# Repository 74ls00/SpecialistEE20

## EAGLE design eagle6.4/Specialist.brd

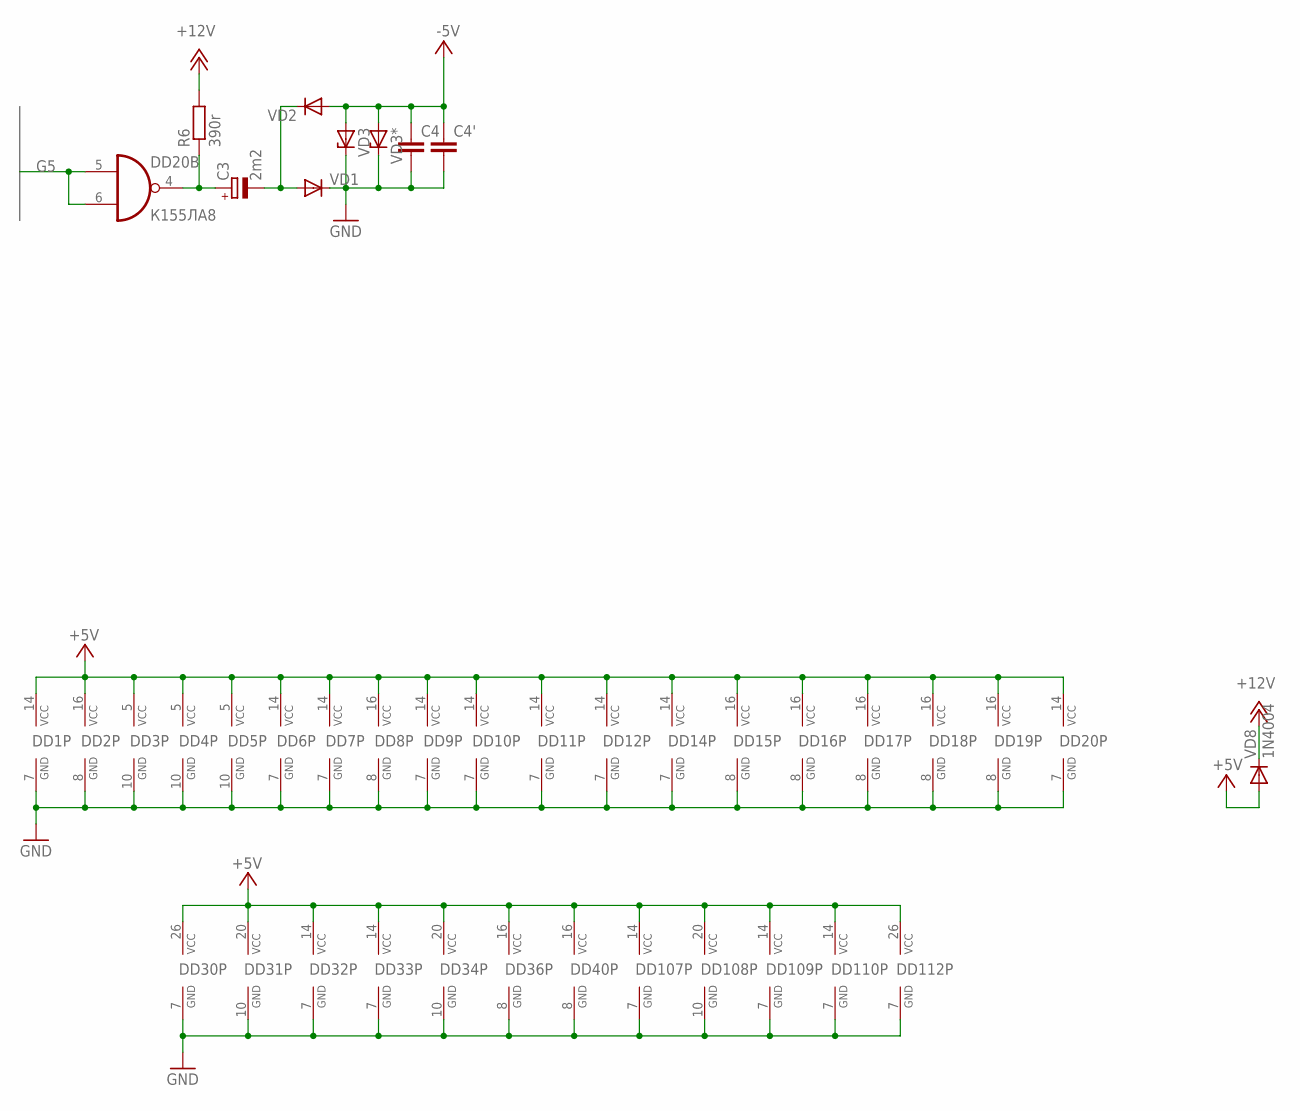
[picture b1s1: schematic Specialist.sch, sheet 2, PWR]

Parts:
C3: 2m2; E2,5-5
C4, C4': C-EUC1206; C1206
DD1, DD9: К155ЛН1; DIL14
DD2, DD8: К155ИЕ7; DIL16
DD3, DD4, DD5: К155ИЕ5; DIL14
DD6, DD107, DD110: К155ЛЕ1; DIL14
DD7: К155ЛА4; DIL14
DD10: К155ЛА2; DIL14
DD11, DD14: К155ЛА3; DIL14
DD12: К155ТМ2; DIL14
DD15, DD16, DD17, DD18: К155КП2; DIL16
DD19: К155ЛП10; DIL16
DD20: К155ЛА8; DIL14
DD30, DD112: КР580ВВ55; DIL40
DD31, DD108: К555ИР22; DIL20
DD32, DD33, DD109: К555ИР16; DIL14
DD34: К555АП6; DIL20
DD36, DD40: К155ИД4; DIL16
R6: 390r; 0411/15
VD1, VD2: DIODE-SOD80C; SOD80C
VD3, VD3*: ZENER-DIODESOD80C; SOD80C
VD8: 1N4004; DO41-10

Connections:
+5V: DD1.14 (VCC), DD2.16 (VCC), DD3.5 (VCC), DD4.5 (VCC), DD5.5 (VCC), DD6.14 (VCC), DD7.14 (VCC), DD8.16 (VCC), DD9.14 (VCC), DD10.14 (VCC), DD11.14 (VCC), DD12.14 (VCC), DD14.14 (VCC), DD15.16 (VCC), DD16.16 (VCC), DD17.16 (VCC), DD18.16 (VCC), DD19.16 (VCC), DD20.14 (VCC), DD30.26 (VCC), DD31.20 (VCC), DD32.14 (VCC), DD33.14 (VCC), DD34.20 (VCC), DD36.16 (VCC), DD40.16 (VCC), DD107.14 (VCC), DD108.20 (VCC), DD109.14 (VCC), DD110.14 (VCC), DD112.26 (VCC), VD8.A; also elsewhere on the board
+12V: R6.2, VD8.C; also elsewhere on the board
-5V: C4.1, C4'.1, VD2.A, VD3.A, VD3*.A; also elsewhere on the board
G5: DD20.5 (I0), DD20.6 (I1); also elsewhere on the board
GND: C4.2, C4'.2, DD1.7 (GND), DD2.8 (GND), DD3.10 (GND), DD4.10 (GND), DD5.10 (GND), DD6.7 (GND), DD7.7 (GND), DD8.8 (GND), DD9.7 (GND), DD10.7 (GND), DD11.7 (GND), DD12.7 (GND), DD14.7 (GND), DD15.8 (GND), DD16.8 (GND), DD17.8 (GND), DD18.8 (GND), DD19.8 (GND), DD20.7 (GND), DD30.7 (GND), DD31.10 (GND), DD32.7 (GND), DD33.7 (GND), DD34.10 (GND), DD36.8 (GND), DD40.8 (GND), DD107.7 (GND), DD108.10 (GND), DD109.7 (GND), DD110.7 (GND), DD112.7 (GND), VD1.C, VD3.C, VD3*.C; also elsewhere on the board
unnamed: C3.+, DD20.4 (O), R6.1
unnamed: C3.-, VD1.A, VD2.C

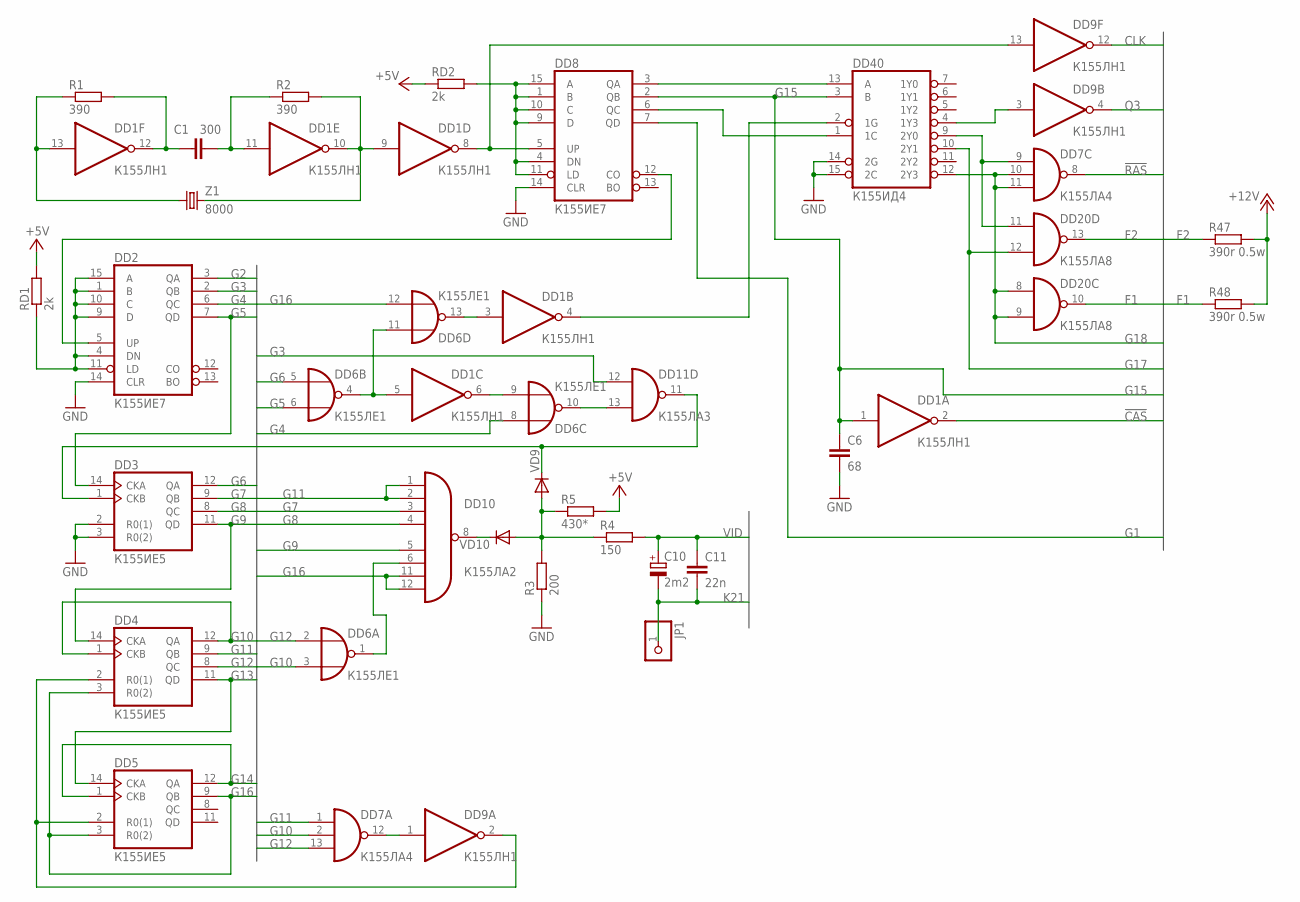
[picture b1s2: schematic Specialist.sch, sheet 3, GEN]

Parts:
C1: 300; C0805
C6: 68; C0805
C10: 2m2; E2,5-5
C11: 22n; C0805
DD1, DD9: К155ЛН1; DIL14
DD2, DD8: К155ИЕ7; DIL16
DD3, DD4, DD5: К155ИЕ5; DIL14
DD6: К155ЛЕ1; DIL14
DD7: К155ЛА4; DIL14
DD10: К155ЛА2; DIL14
DD11: К155ЛА3; DIL14
DD20: К155ЛА8; DIL14
DD40: К155ИД4; DIL16
JP1: PINHD-1X1; 1X01
R1, R2: 390; M1206
R3: 200; M1206
R4: 150; M1206
R5: 430*; M1206
R47, R48: 390r 0.5w; 0411/15
RD1, RD2: 2k; M1206
VD9, VD10: DIODE-SOD80C; SOD80C
Z1: 8000; HC49/S

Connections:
!CAS: DD1.2 (O); also elsewhere on the board
!RAS: DD7.8 (O); also elsewhere on the board
+5V: R5.2, RD1.2, RD2.1; also elsewhere on the board
+12V: R47.2, R48.2; also elsewhere on the board
CLK: DD9.12 (O); also elsewhere on the board
F1: DD20.10 (O), R48.1; also elsewhere on the board
F2: DD20.13 (O), R47.1; also elsewhere on the board
G1: DD8.7 (QD); also elsewhere on the board
G2: DD2.3 (QA); also elsewhere on the board
G3: DD2.2 (QB), DD11.12 (I0); also elsewhere on the board
G4: DD2.6 (QC), DD6.8 (I0); also elsewhere on the board
G5: DD2.7 (QD), DD3.14 (CKA), DD6.6 (I1); also elsewhere on the board
G6: DD3.12 (QA), DD6.5 (I0); also elsewhere on the board
G7: DD3.9 (QB), DD10.3 (I2); also elsewhere on the board
G8: DD3.8 (QC), DD10.4 (I3); also elsewhere on the board
G9: DD3.11 (QD), DD4.14 (CKA), DD10.5 (I4); also elsewhere on the board
G10: DD4.1 (CKB), DD4.12 (QA), DD6.3 (I1), DD7.2 (I1); also elsewhere on the board
G11: DD4.9 (QB), DD7.1 (I0), DD10.1 (I0), DD10.2 (I1); also elsewhere on the board
G12: DD4.8 (QC), DD6.2 (I0), DD7.13 (I2); also elsewhere on the board
G13: DD4.11 (QD), DD5.14 (CKA); also elsewhere on the board
G14: DD5.1 (CKB), DD5.12 (QA); also elsewhere on the board
G15: C6.1, DD1.1 (I), DD8.2 (QB), DD40.3 (B); also elsewhere on the board
G16: DD4.3 (R0(2)), DD5.3 (R0(2)), DD5.9 (QB), DD6.12 (I1), DD10.11 (I6), DD10.12 (I7); also elsewhere on the board
G17: DD20.12 (I1), DD40.10 (2Y1); also elsewhere on the board
G18: DD7.10 (I1), DD7.11 (I2), DD20.8 (I0), DD20.9 (I1), DD40.12 (2Y3); also elsewhere on the board
GND: C6.2, DD2.14 (CLR), DD3.2 (R0(1)), DD3.3 (R0(2)), DD8.14 (CLR), DD40.14 (2G), DD40.15 (2C), R3.1; also elsewhere on the board
K21: C10.-, C11.2, JP1.1
unnamed: DD6.10 (O), DD11.13 (I1)
unnamed: DD1.5 (I), DD6.4 (O), DD6.11 (I0)
unnamed: DD1.13 (I), R1.1, Z1.1
unnamed: DD9.3 (I), DD40.4 (1Y3)
unnamed: C1.1, DD1.12 (O), R1.2
unnamed: DD1.9 (I), DD1.10 (O), R2.2, Z1.2
unnamed: C1.2, DD1.11 (I), R2.1
unnamed: DD1.8 (O), DD8.5 (UP), DD9.13 (I)
unnamed: DD2.5 (UP), DD8.12 (CO)
unnamed: DD6.1 (O), DD10.6 (I5)
unnamed: DD1.6 (O), DD6.9 (I1)
unnamed: DD1.3 (I), DD6.13 (O)
unnamed: DD4.2 (R0(1)), DD5.2 (R0(1)), DD9.2 (O)
unnamed: DD7.9 (I0), DD20.11 (I0), DD40.9 (2Y0)
unnamed: DD8.3 (QA), DD40.13 (A)
unnamed: DD8.6 (QC), DD40.1 (1C)
unnamed: DD1.4 (O), DD40.2 (1G)
unnamed: DD10.8 (O), VD10.C
unnamed: DD3.1 (CKB), DD11.11 (O), VD9.C
unnamed: R3.2, R4.1, R5.1, VD9.A, VD10.A
unnamed: DD2.1 (B), DD2.4 (DN), DD2.9 (D), DD2.10 (C), DD2.11 (LD), DD2.15 (A), RD1.1
unnamed: DD7.12 (O), DD9.1 (I)
unnamed: DD8.1 (B), DD8.4 (DN), DD8.9 (D), DD8.10 (C), DD8.11 (LD), DD8.15 (A), RD2.2
Q3: DD9.4 (O); also elsewhere on the board
VID: C10.+, C11.1, R4.2; also elsewhere on the board

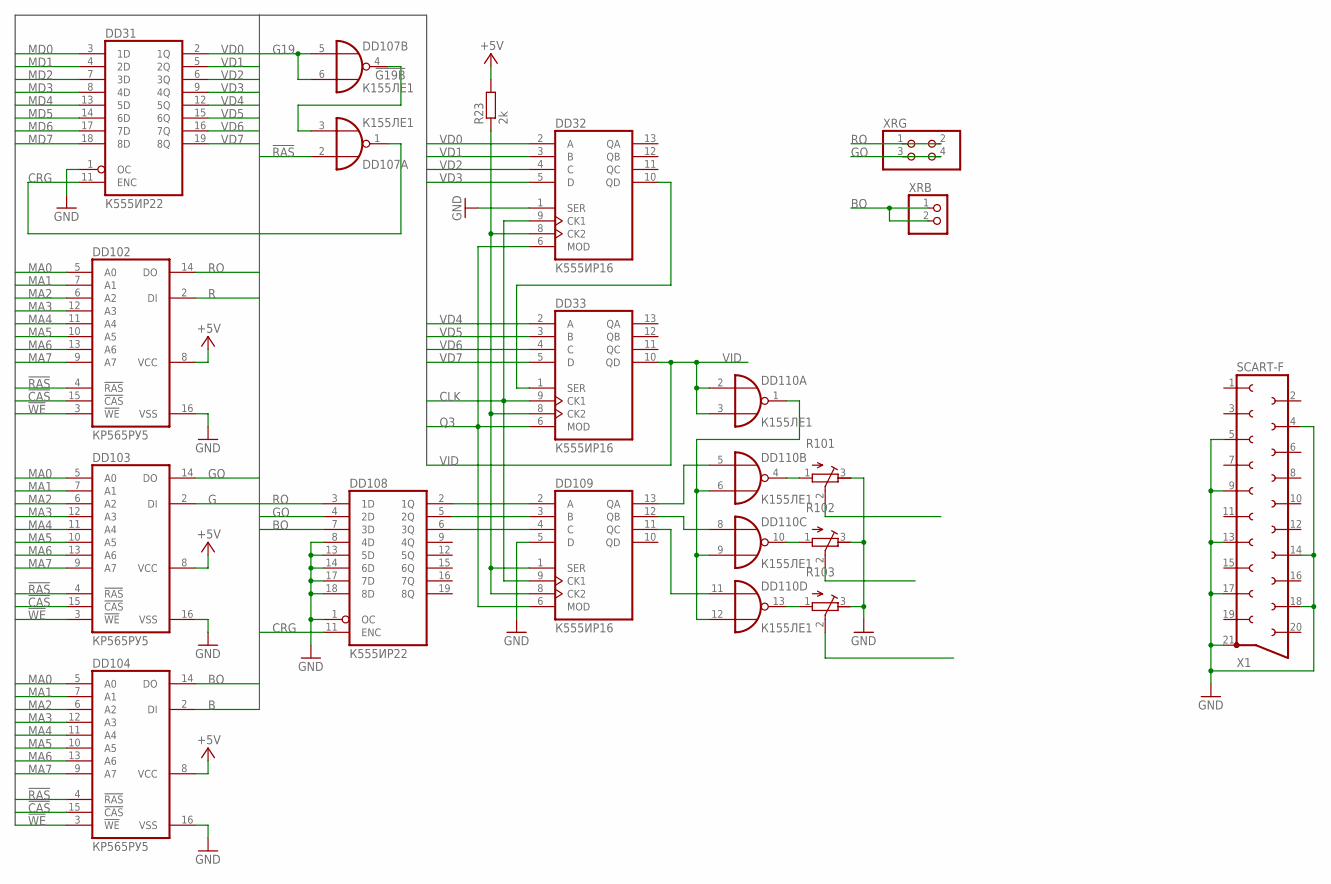
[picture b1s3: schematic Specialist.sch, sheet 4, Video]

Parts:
DD31, DD108: К555ИР22; DIL20
DD32, DD33, DD109: К555ИР16; DIL14
DD102, DD103, DD104: КР565РУ5; DIL16
DD107, DD110: К155ЛЕ1; DIL14
R23: 2k; M1206
R101, R102, R103: R-TRIMM3296W; RTRIM3296W
X1: SCART-F
XRB: PINHD-1X2; 2X01
XRG: PINHD-2X2; 2X02

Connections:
!CAS: DD102.15 (!CAS), DD103.15 (!CAS), DD104.15 (!CAS); also elsewhere on the board
!G19B: DD107.3 (I1), DD107.4 (O)
!RAS: DD102.4 (!RAS), DD103.4 (!RAS), DD104.4 (!RAS), DD107.2 (I0); also elsewhere on the board
!WE: DD102.3 (!WE), DD103.3 (!WE), DD104.3 (!WE); also elsewhere on the board
+5V: DD102.8 (VCC), DD103.8 (VCC), DD104.8 (VCC), R23.2; also elsewhere on the board
B: DD104.2 (DI); also elsewhere on the board
BO: DD104.14 (DO), DD108.7 (3D), XRB.1, XRB.2; also elsewhere on the board
CLK: DD32.9 (CK1), DD33.9 (CK1), DD109.9 (CK1); also elsewhere on the board
CRG: DD31.11 (ENC), DD107.1 (O), DD108.11 (ENC)
G: DD103.2 (DI); also elsewhere on the board
G19: DD107.5 (I0), DD107.6 (I1); also elsewhere on the board
GND: DD31.1 (OC), DD32.1 (SER), DD102.16 (VSS), DD103.16 (VSS), DD104.16 (VSS), DD108.1 (OC), DD108.8 (4D), DD108.13 (5D), DD108.14 (6D), DD108.17 (7D), DD108.18 (8D), DD109.5 (D), R101.3 (E), R102.3 (E), R103.3 (E), X1.4, X1.5, X1.9, X1.13, X1.14, X1.17, X1.18, X1.21; also elsewhere on the board
GO: DD103.14 (DO), DD108.4 (2D), XRG.3, XRG.4; also elsewhere on the board
MA0: DD102.5 (A0), DD103.5 (A0), DD104.5 (A0); also elsewhere on the board
MA1: DD102.7 (A1), DD103.7 (A1), DD104.7 (A1); also elsewhere on the board
MA2: DD102.6 (A2), DD103.6 (A2), DD104.6 (A2); also elsewhere on the board
MA3: DD102.12 (A3), DD103.12 (A3), DD104.12 (A3); also elsewhere on the board
MA4: DD102.11 (A4), DD103.11 (A4), DD104.11 (A4); also elsewhere on the board
MA5: DD102.10 (A5), DD103.10 (A5), DD104.10 (A5); also elsewhere on the board
MA6: DD102.13 (A6), DD103.13 (A6), DD104.13 (A6); also elsewhere on the board
MA7: DD102.9 (A7), DD103.9 (A7), DD104.9 (A7); also elsewhere on the board
MD0: DD31.3 (1D); also elsewhere on the board
MD1: DD31.4 (2D); also elsewhere on the board
MD2: DD31.7 (3D); also elsewhere on the board
MD3: DD31.8 (4D); also elsewhere on the board
MD4: DD31.13 (5D); also elsewhere on the board
MD5: DD31.14 (6D); also elsewhere on the board
MD6: DD31.17 (7D); also elsewhere on the board
MD7: DD31.18 (8D); also elsewhere on the board
unnamed: DD32.10 (QD), DD33.1 (SER)
unnamed: DD110.1 (O), DD110.6 (I1), DD110.9 (I1), DD110.12 (I1)
unnamed: DD108.2 (1Q), DD109.2 (A)
unnamed: DD108.5 (2Q), DD109.3 (B)
unnamed: DD108.6 (3Q), DD109.4 (C)
unnamed: DD109.13 (QA), DD110.5 (I0)
unnamed: DD109.12 (QB), DD110.8 (I0)
unnamed: DD109.11 (QC), DD110.11 (I0)
unnamed: DD110.4 (O), R101.1 (A)
unnamed: DD110.10 (O), R102.1 (A)
unnamed: DD110.13 (O), R103.1 (A)
Q3: DD32.6 (MOD), DD33.6 (MOD), DD109.6 (MOD); also elsewhere on the board
R: DD102.2 (DI); also elsewhere on the board
R2: DD32.8 (CK2), DD33.8 (CK2), DD109.1 (SER), DD109.8 (CK2), R23.1
RO: DD102.14 (DO), DD108.3 (1D), XRG.1, XRG.2; also elsewhere on the board
VD0: DD31.2 (1Q), DD32.2 (A)
VD1: DD31.5 (2Q), DD32.3 (B)
VD2: DD31.6 (3Q), DD32.4 (C)
VD3: DD31.9 (4Q), DD32.5 (D)
VD4: DD31.12 (5Q), DD33.2 (A)
VD5: DD31.15 (6Q), DD33.3 (B)
VD6: DD31.16 (7Q), DD33.4 (C)
VD7: DD31.19 (8Q), DD33.5 (D)
VID: DD33.10 (QD), DD110.2 (I0), DD110.3 (I1); also elsewhere on the board

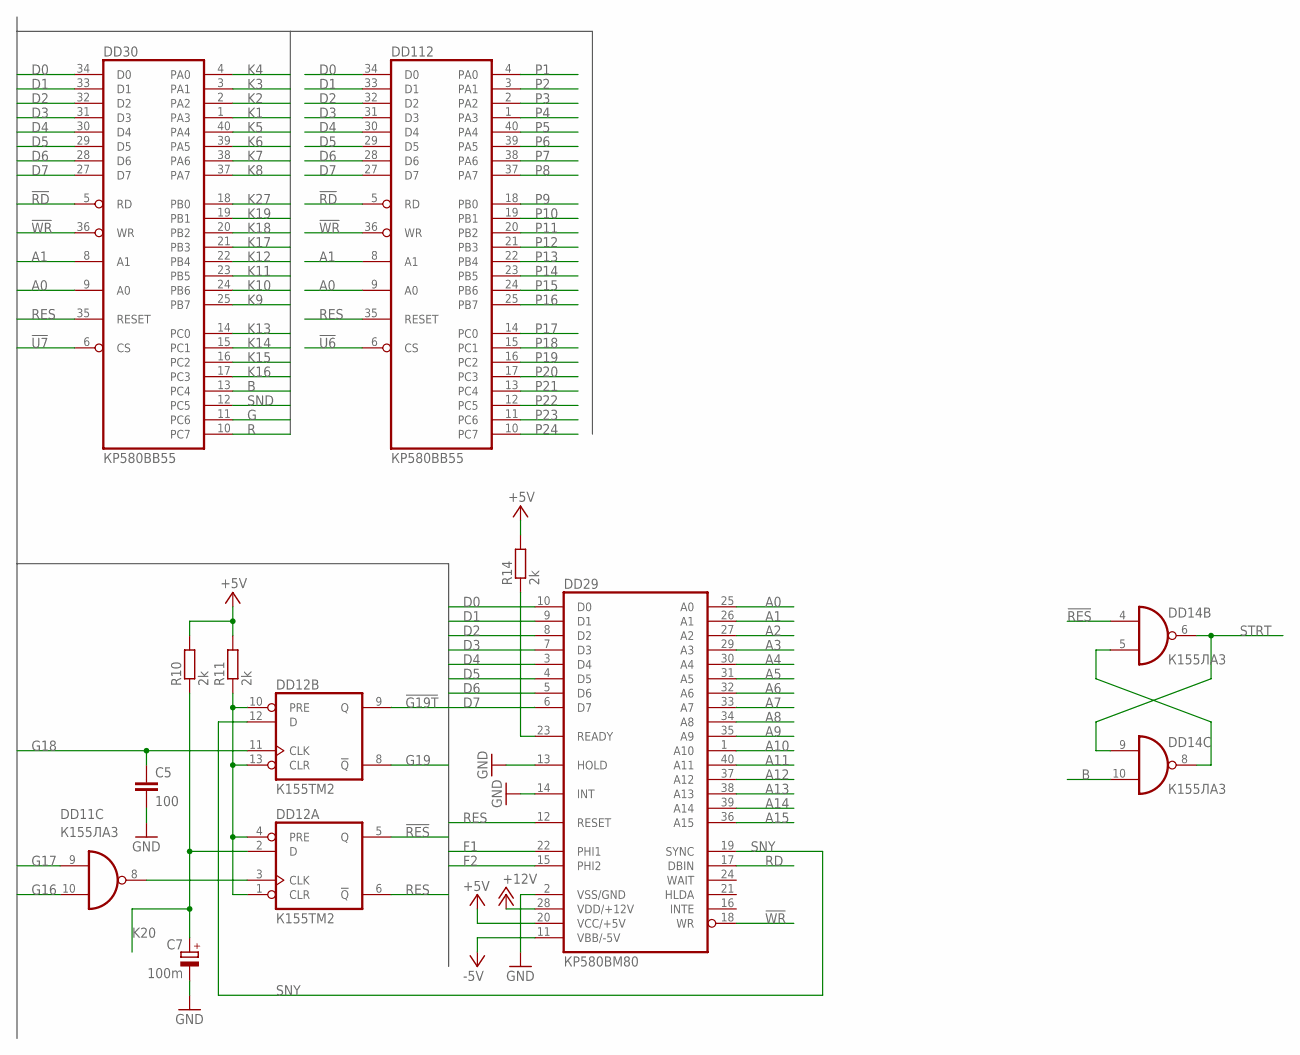
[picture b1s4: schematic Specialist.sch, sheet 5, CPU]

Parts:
C5: 100; C0805
C7: 100m; E2,5-5
DD11, DD14: К155ЛА3; DIL14
DD12: К155ТМ2; DIL14
DD29: КР580ВМ80; DIL40
DD30, DD112: КР580ВВ55; DIL40
R10, R11, R14: 2k; M1206

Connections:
!G19T: DD12.9 (Q); also elsewhere on the board
!RD: DD30.5 (RD), DD112.5 (RD); also elsewhere on the board
!RES: DD12.5 (Q), DD14.4 (I0)
!U6: DD112.6 (CS); also elsewhere on the board
!U7: DD30.6 (CS); also elsewhere on the board
!WR: DD29.18 (WR), DD30.36 (WR), DD112.36 (WR); also elsewhere on the board
+5V: DD29.20 (VCC/+5V), R10.2, R11.2, R14.2; also elsewhere on the board
+12V: DD29.28 (VDD/+12V); also elsewhere on the board
-5V: DD29.11 (VBB/-5V); also elsewhere on the board
A0: DD29.25 (A0), DD30.9 (A0), DD112.9 (A0); also elsewhere on the board
A1: DD29.26 (A1), DD30.8 (A1), DD112.8 (A1); also elsewhere on the board
A2: DD29.27 (A2); also elsewhere on the board
A3: DD29.29 (A3); also elsewhere on the board
A4: DD29.30 (A4); also elsewhere on the board
A5: DD29.31 (A5); also elsewhere on the board
A6: DD29.32 (A6); also elsewhere on the board
A7: DD29.33 (A7); also elsewhere on the board
A8: DD29.34 (A8); also elsewhere on the board
A9: DD29.35 (A9); also elsewhere on the board
A10: DD29.1 (A10); also elsewhere on the board
A11: DD29.40 (A11); also elsewhere on the board
A12: DD29.37 (A12); also elsewhere on the board
A13: DD29.38 (A13); also elsewhere on the board
A14: DD29.39 (A14); also elsewhere on the board
A15: DD29.36 (A15); also elsewhere on the board
B: DD14.10 (I1), DD30.13 (PC4); also elsewhere on the board
D0: DD29.10 (D0), DD30.34 (D0), DD112.34 (D0); also elsewhere on the board
D1: DD29.9 (D1), DD30.33 (D1), DD112.33 (D1); also elsewhere on the board
D2: DD29.8 (D2), DD30.32 (D2), DD112.32 (D2); also elsewhere on the board
D3: DD29.7 (D3), DD30.31 (D3), DD112.31 (D3); also elsewhere on the board
D4: DD29.3 (D4), DD30.30 (D4), DD112.30 (D4); also elsewhere on the board
D5: DD29.4 (D5), DD30.29 (D5), DD112.29 (D5); also elsewhere on the board
D6: DD29.5 (D6), DD30.28 (D6), DD112.28 (D6); also elsewhere on the board
D7: DD29.6 (D7), DD30.27 (D7), DD112.27 (D7); also elsewhere on the board
F1: DD29.22 (PHI1); also elsewhere on the board
F2: DD29.15 (PHI2); also elsewhere on the board
G: DD30.11 (PC6); also elsewhere on the board
G16: DD11.10 (I1); also elsewhere on the board
G17: DD11.9 (I0); also elsewhere on the board
G18: C5.1, DD12.11 (CLK); also elsewhere on the board
G19: DD12.8 (!Q); also elsewhere on the board
GND: C5.2, C7.-, DD29.2 (VSS/GND), DD29.13 (HOLD), DD29.14 (INT); also elsewhere on the board
K1: DD30.1 (PA3); also elsewhere on the board
K2: DD30.2 (PA2); also elsewhere on the board
K3: DD30.3 (PA1); also elsewhere on the board
K4: DD30.4 (PA0); also elsewhere on the board
K5: DD30.40 (PA4); also elsewhere on the board
K6: DD30.39 (PA5); also elsewhere on the board
K7: DD30.38 (PA6); also elsewhere on the board
K8: DD30.37 (PA7); also elsewhere on the board
K9: DD30.25 (PB7); also elsewhere on the board
K10: DD30.24 (PB6); also elsewhere on the board
K11: DD30.23 (PB5); also elsewhere on the board
K12: DD30.22 (PB4); also elsewhere on the board
K13: DD30.14 (PC0); also elsewhere on the board
K14: DD30.15 (PC1); also elsewhere on the board
K15: DD30.16 (PC2); also elsewhere on the board
K16: DD30.17 (PC3); also elsewhere on the board
K17: DD30.21 (PB3); also elsewhere on the board
K18: DD30.20 (PB2); also elsewhere on the board
K19: DD30.19 (PB1); also elsewhere on the board
K20: C7.+, DD12.2 (D), R10.1
K27: DD30.18 (PB0); also elsewhere on the board
unnamed: DD12.1 (CLR), DD12.4 (PRE), DD12.10 (PRE), DD12.13 (CLR), R11.1
unnamed: DD11.8 (O), DD12.3 (CLK)
unnamed: DD14.5 (I1), DD14.8 (O)
unnamed: DD29.23 (READY), R14.1
P1: DD112.4 (PA0); also elsewhere on the board
P2: DD112.3 (PA1); also elsewhere on the board
P3: DD112.2 (PA2); also elsewhere on the board
P4: DD112.1 (PA3); also elsewhere on the board
P5: DD112.40 (PA4); also elsewhere on the board
P6: DD112.39 (PA5); also elsewhere on the board
P7: DD112.38 (PA6); also elsewhere on the board
P8: DD112.37 (PA7); also elsewhere on the board
P9: DD112.18 (PB0); also elsewhere on the board
P10: DD112.19 (PB1); also elsewhere on the board
P11: DD112.20 (PB2); also elsewhere on the board
P12: DD112.21 (PB3); also elsewhere on the board
P13: DD112.22 (PB4); also elsewhere on the board
P14: DD112.23 (PB5); also elsewhere on the board
P15: DD112.24 (PB6); also elsewhere on the board
P16: DD112.25 (PB7); also elsewhere on the board
P17: DD112.14 (PC0); also elsewhere on the board
P18: DD112.15 (PC1); also elsewhere on the board
P19: DD112.16 (PC2); also elsewhere on the board
P20: DD112.17 (PC3); also elsewhere on the board
P21: DD112.13 (PC4); also elsewhere on the board
P22: DD112.12 (PC5); also elsewhere on the board
P23: DD112.11 (PC6); also elsewhere on the board
P24: DD112.10 (PC7); also elsewhere on the board
R: DD30.10 (PC7); also elsewhere on the board
RD: DD29.17 (DBIN); also elsewhere on the board
RES: DD12.6 (!Q), DD29.12 (RESET), DD30.35 (RESET), DD112.35 (RESET); also elsewhere on the board
SND: DD30.12 (PC5); also elsewhere on the board
SNY: DD12.12 (D), DD29.19 (SYNC)
STRT: DD14.6 (O), DD14.9 (I0); also elsewhere on the board

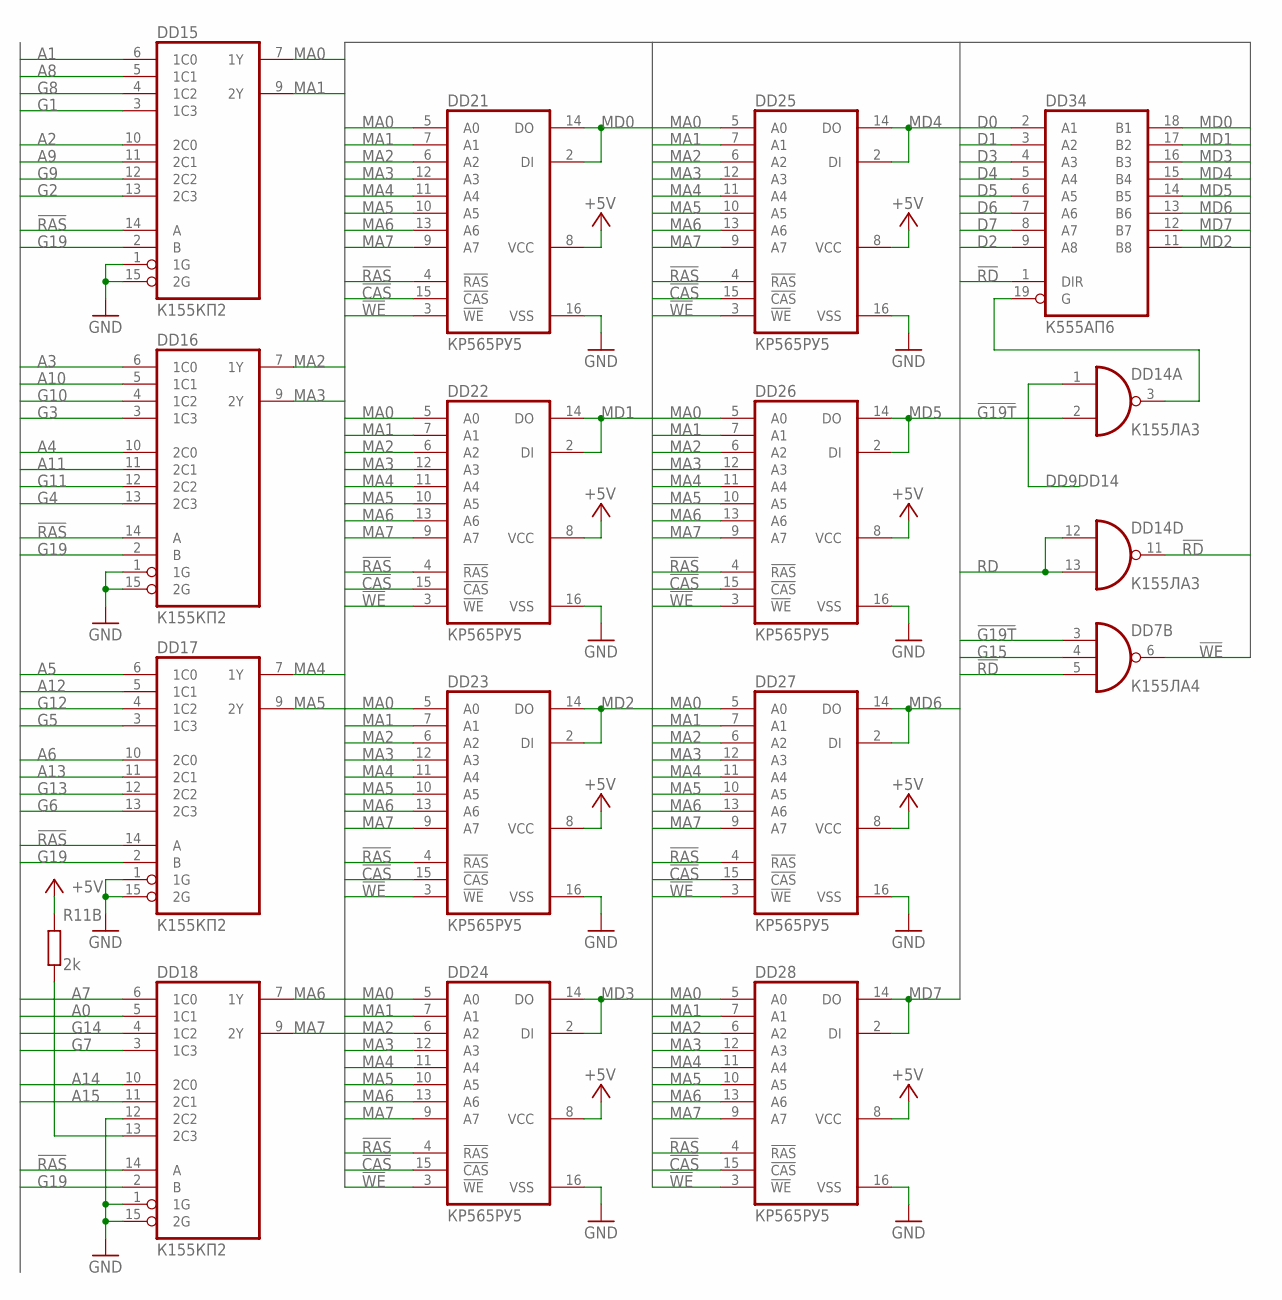
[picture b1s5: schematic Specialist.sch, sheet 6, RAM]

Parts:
DD7: К155ЛА4; DIL14
DD14: К155ЛА3; DIL14
DD15, DD16, DD17, DD18: К155КП2; DIL16
DD21, DD22, DD23, DD24, DD25, DD26, DD27, DD28: КР565РУ5; DIL16
DD34: К555АП6; DIL20
R11B: 2k; M1206

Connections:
!CAS: DD21.15 (!CAS), DD22.15 (!CAS), DD23.15 (!CAS), DD24.15 (!CAS), DD25.15 (!CAS), DD26.15 (!CAS), DD27.15 (!CAS), DD28.15 (!CAS); also elsewhere on the board
!G19T: DD7.3 (I0), DD14.2 (I1); also elsewhere on the board
!RAS: DD15.14 (A), DD16.14 (A), DD17.14 (A), DD18.14 (A), DD21.4 (!RAS), DD22.4 (!RAS), DD23.4 (!RAS), DD24.4 (!RAS), DD25.4 (!RAS), DD26.4 (!RAS), DD27.4 (!RAS), DD28.4 (!RAS); also elsewhere on the board
!RD: DD7.5 (I2), DD14.11 (O), DD34.1 (DIR); also elsewhere on the board
!WE: DD7.6 (O), DD21.3 (!WE), DD22.3 (!WE), DD23.3 (!WE), DD24.3 (!WE), DD25.3 (!WE), DD26.3 (!WE), DD27.3 (!WE), DD28.3 (!WE); also elsewhere on the board
+5V: DD21.8 (VCC), DD22.8 (VCC), DD23.8 (VCC), DD24.8 (VCC), DD25.8 (VCC), DD26.8 (VCC), DD27.8 (VCC), DD28.8 (VCC), R11B.2; also elsewhere on the board
A0: DD18.5 (1C1); also elsewhere on the board
A1: DD15.6 (1C0); also elsewhere on the board
A2: DD15.10 (2C0); also elsewhere on the board
A3: DD16.6 (1C0); also elsewhere on the board
A4: DD16.10 (2C0); also elsewhere on the board
A5: DD17.6 (1C0); also elsewhere on the board
A6: DD17.10 (2C0); also elsewhere on the board
A7: DD18.6 (1C0); also elsewhere on the board
A8: DD15.5 (1C1); also elsewhere on the board
A9: DD15.11 (2C1); also elsewhere on the board
A10: DD16.5 (1C1); also elsewhere on the board
A11: DD16.11 (2C1); also elsewhere on the board
A12: DD17.5 (1C1); also elsewhere on the board
A13: DD17.11 (2C1); also elsewhere on the board
A14: DD18.10 (2C0); also elsewhere on the board
A15: DD18.11 (2C1); also elsewhere on the board
D0: DD34.2 (A1); also elsewhere on the board
D1: DD34.3 (A2); also elsewhere on the board
D2: DD34.9 (A8); also elsewhere on the board
D3: DD34.4 (A3); also elsewhere on the board
D4: DD34.5 (A4); also elsewhere on the board
D5: DD34.6 (A5); also elsewhere on the board
D6: DD34.7 (A6); also elsewhere on the board
D7: DD34.8 (A7); also elsewhere on the board
DD9DD14: DD14.1 (I0); also elsewhere on the board
G1: DD15.3 (1C3); also elsewhere on the board
G2: DD15.13 (2C3); also elsewhere on the board
G3: DD16.3 (1C3); also elsewhere on the board
G4: DD16.13 (2C3); also elsewhere on the board
G5: DD17.3 (1C3); also elsewhere on the board
G6: DD17.13 (2C3); also elsewhere on the board
G7: DD18.3 (1C3); also elsewhere on the board
G8: DD15.4 (1C2); also elsewhere on the board
G9: DD15.12 (2C2); also elsewhere on the board
G10: DD16.4 (1C2); also elsewhere on the board
G11: DD16.12 (2C2); also elsewhere on the board
G12: DD17.4 (1C2); also elsewhere on the board
G13: DD17.12 (2C2); also elsewhere on the board
G14: DD18.4 (1C2); also elsewhere on the board
G15: DD7.4 (I1); also elsewhere on the board
G19: DD15.2 (B), DD16.2 (B), DD17.2 (B), DD18.2 (B); also elsewhere on the board
GND: DD15.1 (1G), DD15.15 (2G), DD16.1 (1G), DD16.15 (2G), DD17.1 (1G), DD17.15 (2G), DD18.1 (1G), DD18.12 (2C2), DD18.15 (2G), DD21.16 (VSS), DD22.16 (VSS), DD23.16 (VSS), DD24.16 (VSS), DD25.16 (VSS), DD26.16 (VSS), DD27.16 (VSS), DD28.16 (VSS); also elsewhere on the board
MA0: DD15.7 (1Y), DD21.5 (A0), DD22.5 (A0), DD23.5 (A0), DD24.5 (A0), DD25.5 (A0), DD26.5 (A0), DD27.5 (A0), DD28.5 (A0); also elsewhere on the board
MA1: DD15.9 (2Y), DD21.7 (A1), DD22.7 (A1), DD23.7 (A1), DD24.7 (A1), DD25.7 (A1), DD26.7 (A1), DD27.7 (A1), DD28.7 (A1); also elsewhere on the board
MA2: DD16.7 (1Y), DD21.6 (A2), DD22.6 (A2), DD23.6 (A2), DD24.6 (A2), DD25.6 (A2), DD26.6 (A2), DD27.6 (A2), DD28.6 (A2); also elsewhere on the board
MA3: DD16.9 (2Y), DD21.12 (A3), DD22.12 (A3), DD23.12 (A3), DD24.12 (A3), DD25.12 (A3), DD26.12 (A3), DD27.12 (A3), DD28.12 (A3); also elsewhere on the board
MA4: DD17.7 (1Y), DD21.11 (A4), DD22.11 (A4), DD23.11 (A4), DD24.11 (A4), DD25.11 (A4), DD26.11 (A4), DD27.11 (A4), DD28.11 (A4); also elsewhere on the board
MA5: DD17.9 (2Y), DD21.10 (A5), DD22.10 (A5), DD23.10 (A5), DD24.10 (A5), DD25.10 (A5), DD26.10 (A5), DD27.10 (A5), DD28.10 (A5); also elsewhere on the board
MA6: DD18.7 (1Y), DD21.13 (A6), DD22.13 (A6), DD23.13 (A6), DD24.13 (A6), DD25.13 (A6), DD26.13 (A6), DD27.13 (A6), DD28.13 (A6); also elsewhere on the board
MA7: DD18.9 (2Y), DD21.9 (A7), DD22.9 (A7), DD23.9 (A7), DD24.9 (A7), DD25.9 (A7), DD26.9 (A7), DD27.9 (A7), DD28.9 (A7); also elsewhere on the board
MD0: DD21.2 (DI), DD21.14 (DO), DD34.18 (B1); also elsewhere on the board
MD1: DD22.2 (DI), DD22.14 (DO), DD34.17 (B2); also elsewhere on the board
MD2: DD23.2 (DI), DD23.14 (DO), DD34.11 (B8); also elsewhere on the board
MD3: DD24.2 (DI), DD24.14 (DO), DD34.16 (B3); also elsewhere on the board
MD4: DD25.2 (DI), DD25.14 (DO), DD34.15 (B4); also elsewhere on the board
MD5: DD26.2 (DI), DD26.14 (DO), DD34.14 (B5); also elsewhere on the board
MD6: DD27.2 (DI), DD27.14 (DO), DD34.13 (B6); also elsewhere on the board
MD7: DD28.2 (DI), DD28.14 (DO), DD34.12 (B7); also elsewhere on the board
unnamed: DD18.13 (2C3), R11B.1
unnamed: DD14.3 (O), DD34.19 (G)
RD: DD14.12 (I0), DD14.13 (I1); also elsewhere on the board

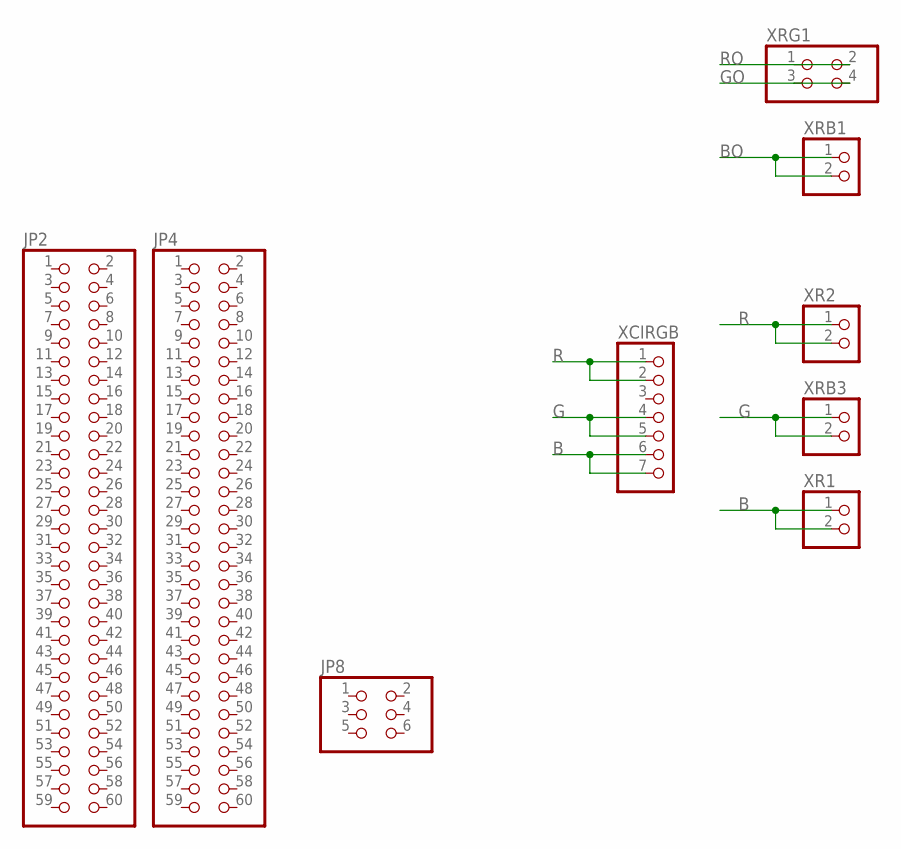
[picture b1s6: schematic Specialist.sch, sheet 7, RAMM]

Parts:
JP2, JP4: PINHD-2X30; 2X30
JP8: PINHD-2X3; 2X03
XCIRGB: PINHD-1X7; 1X07
XR1, XR2: PINHD-1X2; 2X01
XRB1, XRB3: PINHD-1X2; 2X01
XRG1: PINHD-2X2; 2X02

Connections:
B: XCIRGB.6, XCIRGB.7, XR1.1, XR1.2; also elsewhere on the board
BO: XRB1.1, XRB1.2; also elsewhere on the board
G: XCIRGB.4, XCIRGB.5, XRB3.1, XRB3.2; also elsewhere on the board
GO: XRG1.3, XRG1.4; also elsewhere on the board
R: XCIRGB.1, XCIRGB.2, XR2.1, XR2.2; also elsewhere on the board
RO: XRG1.1, XRG1.2; also elsewhere on the board

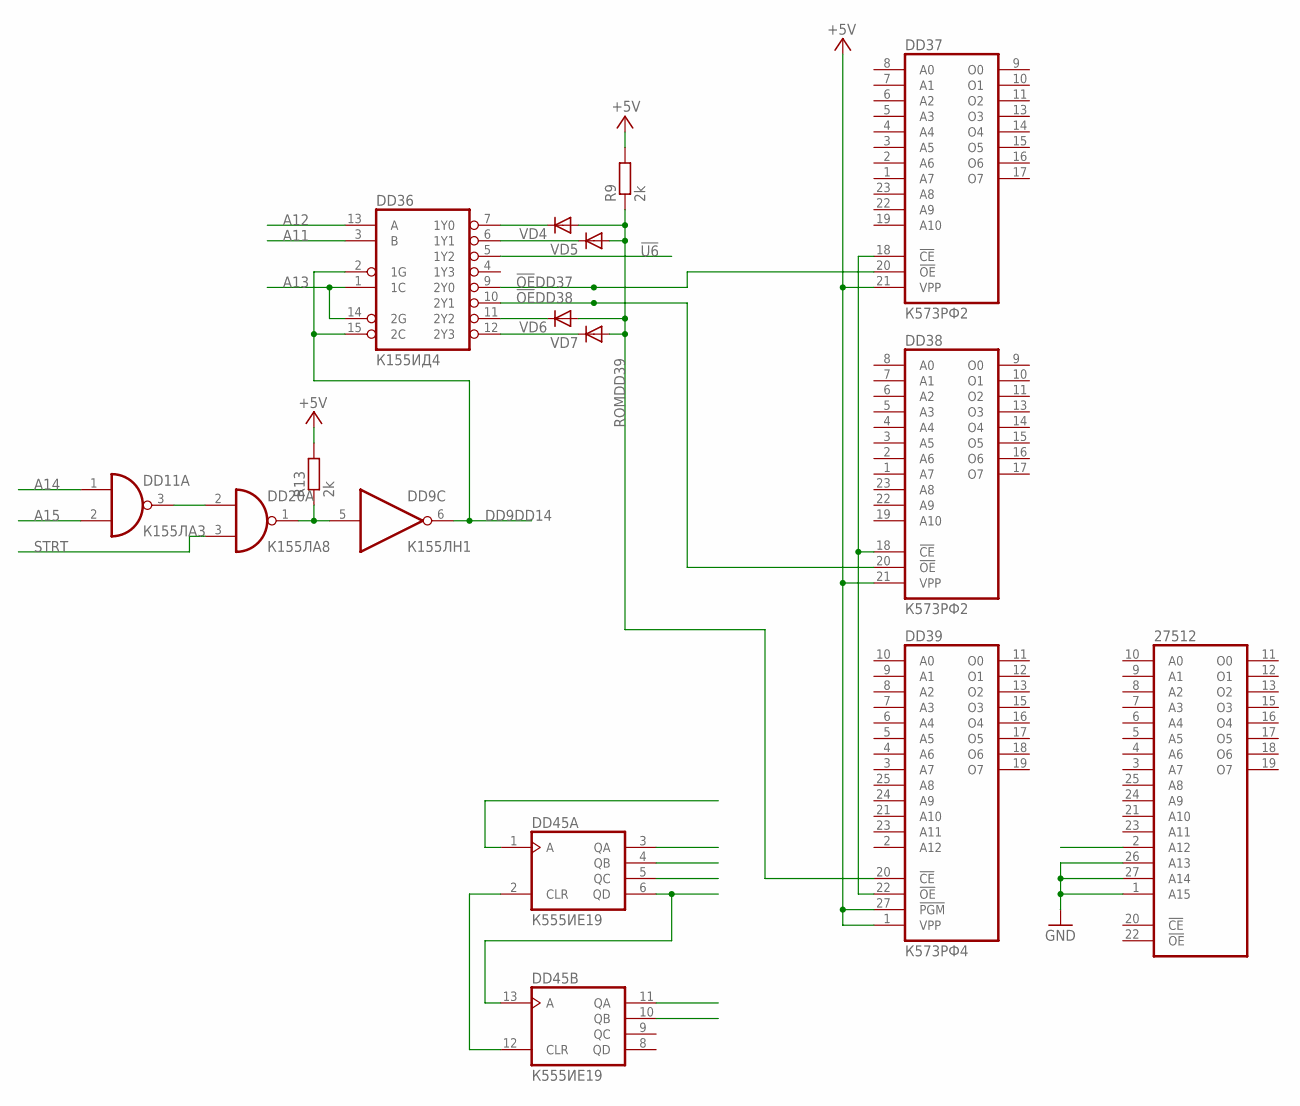
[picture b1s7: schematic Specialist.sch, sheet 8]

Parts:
27512: 27512; DIL28
DD9: К155ЛН1; DIL14
DD11: К155ЛА3; DIL14
DD20: К155ЛА8; DIL14
DD36: К155ИД4; DIL16
DD37, DD38: К573РФ2; DIL24
DD39: К573РФ4; DIL28
DD45: К555ИЕ19; DIL14
R9, R13: 2k; M1206
VD4, VD5, VD6, VD7: DIODE-SOD80C; SOD80C

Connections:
!OE!DD37: DD36.9 (2Y0), DD37.20 (!OE)
!OE!DD38: DD36.10 (2Y1), DD38.20 (!OE)
!U6: DD36.5 (1Y2); also elsewhere on the board
+5V: DD37.21 (VPP), DD38.21 (VPP), DD39.1 (VPP), DD39.27 (!PGM), R9.2, R13.2; also elsewhere on the board
A11: DD36.3 (B); also elsewhere on the board
A12: DD36.13 (A); also elsewhere on the board
A13: DD36.1 (1C), DD36.14 (2G); also elsewhere on the board
A14: DD11.1 (I0); also elsewhere on the board
A15: DD11.2 (I1); also elsewhere on the board
DD9DD14: DD9.6 (O), DD36.2 (1G), DD36.15 (2C); also elsewhere on the board
GND: 27512.1 (A15), 27512.14 (GND), 27512.26 (A13), 27512.27 (A14), DD37.12 (GND), DD38.12 (GND), DD39.14 (GND), DD45.7 (GND); also elsewhere on the board
unnamed: DD36.7 (1Y0), VD4.C
unnamed: DD36.6 (1Y1), VD5.C
unnamed: DD36.11 (2Y2), VD6.C
unnamed: DD36.12 (2Y3), VD7.C
unnamed: DD45.6 (QD), DD45.13 (A)
unnamed: DD37.18 (!CE), DD38.18 (!CE), DD39.22 (!OE)
unnamed: DD11.3 (O), DD20.2 (I0)
unnamed: DD9.5 (I), DD20.1 (O), R13.1
unnamed: DD45.2 (CLR), DD45.12 (CLR)
ROMDD39: DD39.20 (!CE), R9.1, VD4.A, VD5.A, VD6.A, VD7.A
STRT: DD20.3 (I1); also elsewhere on the board
VCC: 27512.28 (VCC), DD37.24 (VCC), DD38.24 (VCC), DD39.28 (VCC), DD45.14 (VCC)
